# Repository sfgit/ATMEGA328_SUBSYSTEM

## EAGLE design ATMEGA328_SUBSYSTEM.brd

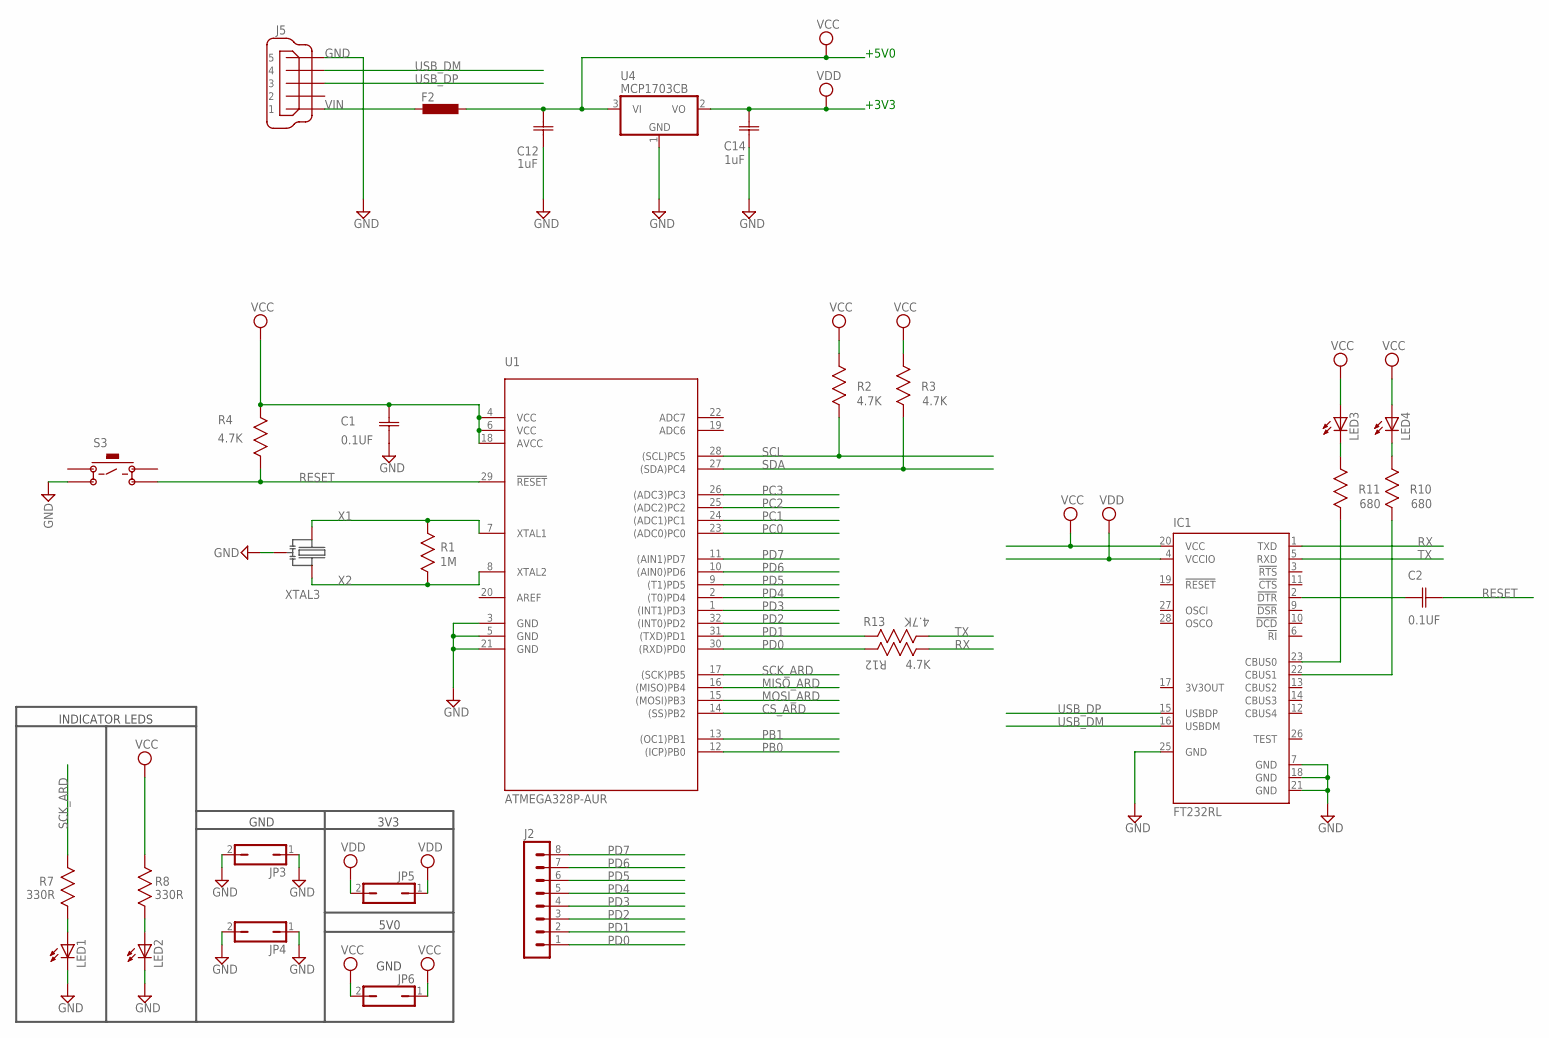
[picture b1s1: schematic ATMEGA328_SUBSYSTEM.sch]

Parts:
C1, C2: 0.1UF; CAPC1608X90N
C12, C14: 1uF; CAPC2013X140N
F2: L-EUL1812; L1812
IC1: FT232RL; SSOP28
J2: MA08-1
J5: MINI-USB-UX60A-MB-5ST; UX60A-MB-5ST
JP3, JP4, JP5, JP6: JP1Q; JP1
LED1, LED2: LEDCHIP-LED0603; CHIP-LED0603
LED3, LED4: LEDCHIPLED_0805; CHIPLED_0805
R1: 1M; RESC1608X60N
R2, R3, R4, R12, R13: 4.7K; RESC1608X60N
R7, R8: 330R; RESC1608X60N
R10, R11: 680; RESC1608X60N
S3: 1825910-6-SPST-NOPB-4P; SW-NOPB-4
U1: ATMEGA328P-AUR; TQFP-32; PARTNO ATMEGA328P-AUR
U4: MCP1703CB; SOT23
XTAL3: CSTCE16M0V53-R0

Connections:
GND: C1.1 (C1), C12.1 (C1), C14.1 (C1), IC1.7 (GND), IC1.18 (GND), IC1.21 (GND), IC1.25 (GND), J5.5, JP3.1, JP3.2, JP4.1, JP4.2, LED1.C, LED2.C, S3.2, U1.3 (GND), U1.5 (GND), U1.21 (GND), U4.1 (GND), XTAL3.2
MISO_ARD: U1.16 ((MISO)PB4)
MOSI_ARD: U1.15 ((MOSI)PB3)
unnamed: IC1.23 (CBUS0), R11.2 (R2)
unnamed: C2.2 (C2), IC1.2 (!DTR)
unnamed: IC1.22 (CBUS1), R10.2 (R2)
unnamed: LED3.C, R11.1 (R1)
unnamed: LED4.C, R10.1 (R1)
unnamed: LED2.A, R8.2 (R2)
unnamed: LED1.A, R7.2 (R2)
PB0: U1.12 ((ICP)PB0)
PB1: U1.13 ((OC1)PB1)
PC0: U1.23 ((ADC0)PC0)
PC1: U1.24 ((ADC1)PC1)
PC2: U1.25 ((ADC2)PC2)
PC3: U1.26 ((ADC3)PC3)
PD0: J2.1, R12.1 (R1), U1.30 ((RXD)PD0)
PD1: J2.2, R13.1 (R1), U1.31 ((TXD)PD1)
PD2: J2.3, U1.32 ((INT0)PD2)
PD3: J2.4, U1.1 ((INT1)PD3)
PD4: J2.5, U1.2 ((T0)PD4)
PD5: J2.6, U1.9 ((T1)PD5)
PD6: J2.7, U1.10 ((AIN0)PD6)
PD7: J2.8, U1.11 ((AIN1)PD7)
RESET: C2.1 (C1), R4.2 (R2), S3.4, U1.29 (!RESET)
RX: IC1.1 (TXD), R12.2 (R2)
SCK_ARD: R7.1 (R1), U1.17 ((SCK)PB5)
SCL: R2.2 (R2), U1.28 ((SCL)PC5)
SDA: R3.2 (R2), U1.27 ((SDA)PC4)
TX: IC1.5 (RXD), R13.2 (R2)
USB_DM: IC1.16 (USBDM), J5.4
USB_DP: IC1.15 (USBDP), J5.3
VCC: C1.2 (C2), C12.2 (C2), F2.1, IC1.20 (VCC), JP6.1, JP6.2, LED3.A, LED4.A, R2.1 (R1), R3.1 (R1), R4.1 (R1), R8.1 (R1), U1.4 (VCC), U1.6 (VCC), U1.18 (AVCC), U4.3 (VI)
VDD: C14.2 (C2), IC1.4 (VCCIO), JP5.1, JP5.2, U4.2 (VO)
VIN: F2.2, J5.1
X1: R1.2 (R2), U1.7 (XTAL1), XTAL3.1
X2: R1.1 (R1), U1.8 (XTAL2), XTAL3.3

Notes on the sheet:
GND
3V3
5V0
INDICATOR LEDS
+5V0
+3V3

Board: 2 copper layers, 30 parts (0 on the bottom side), 29 nets, no tracks yet.

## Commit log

2016-11-05 initial commit
    first past committing design
2016-11-05 adding PDF
2016-11-05 Adding PCB PDF
2016-11-05 Uploading PDFs
2016-11-05 updating pdf
2016-11-05 updating print settings
2016-11-05 uploading blocks
2016-12-14 Deleted backup files
    Deleted backups of the design, not needed
